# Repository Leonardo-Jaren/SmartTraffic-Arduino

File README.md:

# SmartTraffic Arduino

Sistema educativo para explorar una maqueta de seis intersecciones, simular vehículos y consultar un Arduino UNO por USB. El frontend usa Vue 3, Vite y Three.js; la API y el puente local usan Django REST Framework y pySerial.

La maqueta física mide **160 cm de ancho × 120 cm de fondo** según indicó el usuario; el tablero 3D se ajusta a ese tamaño. La distribución interna es una **aproximación** basada en el croquis. Las direcciones H1 ←, H2 →, V1 ↑, V2 ↓ y V3 ↑ fueron confirmadas. La escena base tiene exactamente seis semáforos fijos, uno por cruce, en los puntos y mirando en los sentidos marcados: S1→I1 al sur, S2→I2 al este, S3→I3 al sur, S4→I4 al oeste, S5→I5 al norte y S6→I6 al oeste. La simulación aplica la fase del eje observado en cada luz. El mapa eléctrico del Arduino no está confirmado y el sketch arranca en rojo hasta revisar el cableado.

## Requisitos

- Python 3.12 o superior compatible con las versiones de `backend/requirements.txt`.
- Node.js `^22.18.0` o `>=24.12.0`, npm y un navegador con WebGL.
- Para USB: Arduino UNO R3, cable USB de datos y permiso para acceder al puerto. Django y el puente deben ejecutarse en la computadora que tiene el Arduino conectado.

## Instalar y ejecutar

En una terminal, desde la raíz del repositorio:

```bash
cd backend
python3 -m venv env
./env/bin/python -m pip install -r requirements.txt
./env/bin/python manage.py migrate
./env/bin/python manage.py runserver 127.0.0.1:8000
```

En otra terminal:

```bash
cd frontend
npm ci
npm run dev
```

Abre la dirección local que Vite imprime en su terminal. En Windows sustituye `./env/bin/python` por `env\Scripts\python.exe`. Vite envía las peticiones `/api` a Django mediante su proxy de desarrollo. La API no tiene autenticación: esta configuración es **solo para desarrollo local** y no debe exponerse a Internet.

## Sin Arduino

Selecciona **Simulación**. Puedes pausar, reiniciar, ocultar vehículos, variar cantidad y velocidad, seleccionar y cerrar un tramo, seleccionar un cruce y añadir luces virtuales. Los vehículos buscan otra ruta o salida y, si no existe, esperan; un vehículo que ya está en un tramo cerrado se detiene. La tabla de intersecciones muestra fases virtuales H/V, no el estado físico de S1–S6.

Los autos frenan con el frente detrás de la línea, mantienen espacio en las colas y esperan antes de entrar si no hay lugar para salir del cruce. Un vehículo que ya recibió paso termina de despejarlo aunque cambie la fase. Las calles conservan un color neutro salvo selección o cierre; los colores de paso se muestran en las luces. Los accesos perpendiculares sin luz física tienen señales visuales de ceda el paso; la simulación sigue reservando fases H/V para evitar movimientos incompatibles.

Usa **Pantalla completa** sobre la maqueta para ampliar la vista y conservar los controles de simulación y selección. Puedes volver con el botón de salida o con Escape. Si el navegador no permite la pantalla completa nativa, la vista se amplía dentro de la ventana.

Selecciona S1–S6 en el modelo o en su tarjeta para cambiar su esquina dentro del cruce y girarlo en pasos de 90°. La distribución visual se guarda en este navegador y puede restaurarse. Estos movimientos no cambian el cruce asignado, el eje de simulación ni los pines del Arduino. Un traslado a otro cruce requiere revisar también esa asignación lógica y el montaje físico.

La escala de cálculo es **1 unidad 3D = 5 metros simulados**. Por ejemplo, a 30 km/h se recorren 8,33 m/s, es decir 1,67 unidades 3D/s. Esta conversión de velocidad es independiente del tamaño visual del tablero de 160 × 120 cm. Los desfases horizontales usan 30 km/h como velocidad objetivo virtual; no se ha validado una ola verde física.

## Conectar un Arduino por USB

1. Sigue [electrónica y conexiones](docs/ELECTRONICA.md) y [código Arduino](docs/CODIGO_ARDUINO.md). El sketch arranca en rojo mientras `MAPA_CONFIRMADO` sea `false`.
2. Conecta el UNO a la **misma computadora que ejecuta Django**. Cierra el monitor serial del IDE antes de abrir el puente.
3. En otra terminal del backend ejecuta:

```bash
./env/bin/python manage.py puente_serial --listar
./env/bin/python manage.py puente_serial --puerto /dev/ttyACM0
```

Reemplaza el puerto por el que aparezca en tu equipo, por ejemplo `COM3` en Windows. Selecciona **Dispositivo** en la web: solo se muestran colores informados recientemente por el dispositivo. Un cambio de tiempos queda pendiente hasta recibir `ACK, …, APLICADO`.

Para probar el puente sin hardware en Linux/macOS, ejecuta `./env/bin/python scripts/simulador_arduino.py`, toma el puerto `/dev/pts/...` que muestra y pásalo a `puente_serial --puerto`. La interfaz lo identifica como **simulador serial**, no como Arduino físico.

## Pruebas

```bash
cd backend && ./env/bin/python manage.py test trafico.tests
cd ../frontend && npm test && npm run build
npx playwright install chromium   # una vez, para las pruebas de navegador
npm run test:e2e
cd .. && python3 arduino/tests/test_firmware.py
```

Las pruebas de navegador reutilizan Django y Vite si ya están funcionando localmente, o los arrancan si faltan; en CI necesitan los puertos libres. Se puede indicar un Chromium ya instalado con `CHROMIUM_PATH=/ruta/a/chromium npm run test:e2e`. Los resultados y límites están en [pruebas](docs/PRUEBAS.md).

## Documentación

- [Configuración en otra computadora y exportación de la PCB](docs/CONFIGURACION.md)
- [Análisis de la maqueta y mapa](docs/ANALISIS_MAQUETA.md)
- [Electrónica y tabla de conexiones](docs/ELECTRONICA.md)
- [Guía visual PDF para soldar y conectar los seis semáforos](docs/GUIA_VISUAL_CONEXIONES_ARDUINO.pdf)
- [Código completo para Arduino IDE](docs/CODIGO_ARDUINO.md)
- [Arquitectura, protocolo y modos](docs/ARQUITECTURA.md)
- [Pruebas y limitaciones](docs/PRUEBAS.md)

La guía PDF conserva las orientaciones del diseño anterior con todos los ejes H. Para la posición y la cara actuales de cada semáforo usa [el mapa actualizado](docs/ANALISIS_MAQUETA.md); la correspondencia física de los pines sigue pendiente de comprobación.

El modelo es procedural en Three.js, con tramos y cruces seleccionables; no se exportó un GLB. La comunicación Wi-Fi con ESP32 es una arquitectura futura, no una funcionalidad implementada.

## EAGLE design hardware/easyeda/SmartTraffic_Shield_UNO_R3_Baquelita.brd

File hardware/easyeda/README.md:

# Shield SmartTraffic para Arduino UNO R3

## Variante para baquelita de una cara

- [PCB editable para EasyEDA Standard](SmartTraffic_Shield_UNO_R3_Baquelita_EasyEDA.json).
- [PCB editable en formato Eagle](SmartTraffic_Shield_UNO_R3_Baquelita.brd) y [su esquema con las nueve borneras](SmartTraffic_Shield_UNO_R3_Baquelita.sch).
- [Máscara exportada directamente desde EasyEDA](../../output/pdf/SmartTraffic_Borneras_EasyEDA_1a1.pdf) y [captura de la placa guardada](../../output/imagen/SmartTraffic_EasyEDA_Borneras.png).
- [PDF A4 a escala 1:1 con un único dibujo de cobre](../../output/pdf/SmartTraffic_PCB_Baquelita_1_Cara_1a1.pdf).
- [Vista ampliada de las pistas anchas y sus componentes](../../output/imagen/SmartTraffic_Baquelita_Pistas_Anchas.png). Las imágenes de `Vistas_SmartTraffic` muestran la revisión anterior con U1 SMD.

La baquelita se corta por el rectángulo exterior de **130 × 90 mm**. El UNO R3 de referencia (68,58 × 53,34 mm) queda centrado debajo del shield, con 30,71 mm a cada lado y 18,33 mm arriba y abajo. J1–J4 y los cuatro taladros de montaje conservan sus posiciones de apilado. X1–X6 quedan por encima de la fila digital y X7–X9 por debajo de la analógica, con la entrada de cable hacia el borde correspondiente. El traductor U1, J5, JP1, R1, C1 y C2 quedan a la derecha del UNO. El modelo del ESP32 y su soporte siguen pendientes.

Las 26 redes usan cobre inferior de 0,60 mm de ancho. La separación mínima entre pistas de redes distintas es 1,127 mm. Al incluir los pads, el mínimo nominal es 0,644 mm entre D2 y D3. El rectángulo en BoardOutLine es la línea mecánica de corte. El PDF A4 reúne esa línea, el cobre y las cuatro cruces de montaje en un solo dibujo a escala real.

U1 es el TXU0202DCUR montado sobre un adaptador VSSOP-8 a DIP-8 de paso 2,54 mm y 7,62 mm entre filas, como el PA0042 con pines instalados. Alinea el pin 1 del adaptador con el pad cuadrado de U1. R1 es axial de 10 kΩ con paso de 7,62 mm. C1 y C2 son cerámicos radiales de 100 nF con paso de 5,08 mm. El adaptador y los componentes pasantes se montan en la cara sin cobre. [Adaptador PA0042](https://www.proto-advantage.com/store/datasheets/PA0042.pdf)

Para revisar la versión nueva en EasyEDA Standard, usa **Archivo → Abrir → EasyEDA** con el JSON de baquelita. Comprueba que se vean los ocho orificios de U1 y ejecuta **Check DRC**. Para la transferencia, el PDF incluido usa la vista desde la cara sin cobre. Imprime en A4 al 100 %, coteja la barra de 50 mm y coloca el tóner hacia el cobre sin aplicar un espejo adicional. Marca el corte por el centro de la línea exterior y los cuatro taladros por sus cruces en la misma hoja A4. [DRC de EasyEDA](https://docs.easyeda.com/en/PCB/Design-Rule-Check/)

La máscara incluye guías blancas de 0,30 mm. El CAD indica taladros de 1,20 mm para X1–X9, 1,00 mm para U1 y las tiras, 0,80 mm para R1, C1 y C2, y 3,20 mm para el montaje. Comprueba los diámetros contra las patas y espadines reales. El [exportador](exportar_baquelita.py) coteja las redes con el esquema UART y comprueba continuidad con una pérdida de cobre simulada de 0,04 mm por borde y un margen de perforación de 0,10 mm. Para regenerar el PDF desde la raíz, ejecuta `python hardware/easyeda/exportar_baquelita.py` con ReportLab y Shapely instalados.

La PCB guardada en **Smart traffic** mostró 19 componentes, 26/26 redes y 0 errores de DRC. La máscara nativa se exportó con el borde, el cobre inferior y los pads multicapa en negro, sin espejo. A 600 ppp se cotejaron los 70 orificios y la conectividad entre todos los pares de pads con el esquema. La hoja A4 lleva una sola máscara y guías de perforación pequeñas para taladrar a mano. En ambos casos usa tamaño real. Antes de grabar, verifica la escala, el encaje en el UNO y el montaje de las piezas con la hoja A4.

### Borneras de señal X1–X9

La huella elegida corresponde a **Phoenix Contact 1984617, PT 1,5/2-3,5-H**. Paso de 3,50 mm, cuerpo de 7,00 × 7,55 mm, taladro de 1,20 mm. Ambas filas dejan 3,00 mm nominales entre los cuerpos de borneras vecinas. Presenta las nueve piezas en papel y comprueba acceso del cable y del destornillador con los conectores instalados. Las piezas de 5,00 o 5,08 mm requieren otro patrón. [Ficha del fabricante](https://www.phoenixcontact.com/en-lt/products/printed-circuit-board-terminal-pt-15-2-35-h-1984617)

| Bornera | Pad 1 cuadrado | Pad 2 redondo |
| --- | --- | --- |
| X1 | D13 | D12 |
| X2 | D11 | D10 |
| X3 | D9 | D8 |
| X4 | D7 | D6 |
| X5 | D5 | D4 |
| X6 | D3 | D2 |
| X7 | A0 | A1 |
| X8 | A2 | A3 |
| X9 | A4 (SDA) | A5 (SCL) |

D0/RX y D1/TX pasan por el traductor U1 hasta J5 y quedan reservados para el ESP32. A0 y A1 son pines diferentes. Cada tornillo de X1–X9 lleva **una señal independiente**. El par de tornillos de una bornera carece de retorno común. D13 comparte el LED integrado del UNO. A4/A5 también sirven para I²C y se previeron para supervisión. Su acceso en X9 permite medirlos. Confirma su función antes de asignarlos a luces.

Las borneras entregan GPIO directos. Antes de conectar un foco comprueba polaridad, resistencia instalada, corriente por salida, por puerto y total, retorno y fuente de luces. Si la carga requiere driver, conecta la señal del borne a la entrada del driver y alimenta las luces desde la etapa dimensionada. Mantén la resistencia que ya lleva cada LED. Las luces individuales S1–S9 quedan pendientes del mapa físico y de las mediciones. S4 y S6 requieren salidas independientes.

### Encaje sobre el UNO R3

La comparación con el [CAD oficial A000066](https://docs.arduino.cc/hardware/uno-rev3) verificó la posición de los 32 contactos de J1–J4 y de los cuatro agujeros de montaje. Visto desde arriba con el USB a la izquierda, el pad cuadrado de J1 corresponde a D8 y el de J2 a D0/RX. Los pads cuadrados de J3 y J4 quedan a la izquierda y corresponden a la posición sin conexión de POWER y a A0. Entre los contactos más próximos de J1 y J2 hay 4,064 mm de centro a centro. Usa cuatro tiras separadas para respetar esa separación. [Pinout del UNO R3](https://docs.arduino.cc/resources/pinouts/A000066-full-pinout.pdf)

Para comprobar el apilado y el corte de esta variante, imprime la [hoja de 130 × 90 mm](../../output/pdf/SmartTraffic_PCB_Baquelita_1_Cara_1a1.pdf) al 100 % y mide la barra de 50 mm. Presenta las cuatro tiras en el UNO apagado y verifica que el papel calce sin forzarlas. Después mide la separación con las tiras que vas a soldar. Las soldaduras y las puntas de las patas pasantes quedan del lado del cobre, hacia el UNO. Comprueba la holgura sobre el USB-B, el jack DC, el ATmega328P y ambos ICSP, incluido el que queda junto al USB. El contorno también cubre el botón RESET. Revisa el acceso si necesitas accionarlo con el shield puesto. Si algo toca, elige tiras más altas y repite la prueba antes de transferir el cobre.

## Diseño de referencia de dos caras

Borrador para EasyEDA Standard. El proyecto existente **Smart traffic** contiene el esquema `Sheet_1` y la PCB `SmartTraffic_Shield_UNO_R3`. Para repetir la importación desde los archivos locales, abre **Archivo → Abrir → Eagle**.

La [PCB nativa de EasyEDA](SmartTraffic_Shield_UNO_R3_EasyEDA.json) conserva la revisión exportada del lienzo. Ábrela con **Archivo → Abrir → EasyEDA**. El [PDF A4 a escala 1:1](../../output/pdf/SmartTraffic_PCB_Escala_1a1.pdf) incluye ambas caras para comprobar el encaje en papel. Los archivos Eagle conservan las leyendas del borrador. La revisión nativa exportada carecía de esas dos leyendas de serigrafía.

La PCB contiene los diez componentes del esquema, ocho redes trazadas y un plano inferior de GND. EasyEDA mostró **8/8 redes y 0 errores de DRC** con las reglas del borrador. La comprobación geométrica local encontró continuidad y una separación mínima de 0,170 mm entre cobres de redes distintas. Habrá que repetir el DRC con las reglas del fabricante cuando estén todas las salidas. [Guía de importación](https://docs.easyeda.com/en/Import/Import-Eagle/) · [DRC de EasyEDA](https://docs.easyeda.com/en/PCB/Design-Rule-Check/)

La extracción de bibliotecas notificó siete símbolos rechazados, aunque las diez referencias y sus huellas quedaron visibles en el esquema y la PCB guardados. Al comparar ambos documentos, EasyEDA mostró que los componentes coincidían. La única propuesta fue añadir 28 redes de un solo pin para los contactos del UNO pendientes de asignar. La comparación se cerró sin aplicar esos cambios.

El contorno de 68,58 × 53,34 mm, los cuatro agujeros de 3,2 mm y las posiciones de J1–J4 proceden del CAD **UNO-TH Rev3e** de Arduino. Los centros de las cuatro tiras coinciden con el CAD. Las zonas del USB-B, el jack DC y el ICSP están marcadas en la capa de documentación para comprobar la altura libre al apilar el shield. Los taladros de 1 mm de las tiras se deben cotejar con el conector que se vaya a usar. La geometría adaptada del CAD de Arduino conserva su licencia CC BY-SA 4.0. [CAD del UNO R3](https://docs.arduino.cc/hardware/uno-rev3) · [Licencia](https://creativecommons.org/licenses/by-sa/4.0/)

## UART propuesta

El TXU0202 traduce las señales de 5 V del UNO y de 3,3 V del ESP32 en ambos sentidos. Su lado de 5 V toma alimentación del UNO y el lado de 3,3 V recibe la referencia del ESP32 en J5. Cada lado tiene un condensador de 100 nF. El ESP32 requiere su propia alimentación, dimensionada para el módulo elegido. [Aplicación UART de Texas Instruments](https://www.ti.com/lit/ds/symlink/txu0202.pdf)

| J5 | Conexión del lado ESP32 |
| --- | --- |
| 1 | GND común |
| 2 | Referencia de 3,3 V para el traductor |
| 3 | RX del ESP32 |
| 4 | TX del ESP32 |

Deja JP1 abierto durante la carga del sketch o el uso del puerto serie por USB. R1 mantiene el traductor deshabilitado con el puente abierto. Cierra JP1 para usar la UART con el ESP32 cuando el puerto serie USB esté libre. El conversor USB del UNO comparte D0 y D1. [Esquema oficial del UNO R3](https://docs.arduino.cc/resources/schematics/A000066-schematics.pdf)

## Reparto provisional de salidas

El punto de partida son **27 canales independientes**. S4 y S6 necesitan tiempos distintos para la ola verde. Cualquier agrupación posterior requiere demostrar coincidencia por color durante fases, cierres, arranque y pruebas individuales.

El UNO conserva el control del calendario de fases y el ESP32 mantiene el enlace Wi-Fi y aplica las fases de los cruces delegados. Mantener juntas las luces de un mismo cruce permite ejecutar el amarillo y el intervalo de todo rojo con un solo reloj local.

| Equipo de referencia | Canales para luces | Comunicación y reserva |
| --- | --- | --- |
| UNO R3 | 15 con D2–D12 y A0–A3 como salidas digitales | D0/D1 para UART. A4/A5 para supervisión. D13 queda disponible para una función que tolere el LED de la placa. |
| ESP32-S3-DevKitC-1 | 12 con GPIO4–GPIO15 | GPIO16/17 como candidatos a RX/TX de una UART adicional. GPIO18/21 para supervisión. |

Con el croquis del repositorio como hipótesis, el UNO puede llevar los dos cruces con S4 y S6 completos más un cruce de un solo semáforo. El ESP32 puede llevar el tercer cruce con dos semáforos y los otros dos cruces de una sola cabeza. El esquema todavía carece de asignaciones de los LED a estos pines. El reparto 18/9 también cubre las luces, pero ocupa las 18 E/S del UNO disponibles tras reservar la UART. [Pinout del UNO R3](https://docs.arduino.cc/resources/pinouts/A000066-full-pinout.pdf) · [Pines del ESP32-S3-DevKitC-1](https://docs.espressif.com/projects/esp-dev-kits/en/latest/esp32s3/esp32-s3-devkitc-1/user_guide_v1.1.html)

### Cruces según el croquis v2.1 del repositorio

| Cruce | Semáforos y sentido regulado según el croquis |
| --- | --- |
| I1 | S1, V1 hacia el norte |
| I2 | S2, H1 hacia el oeste. S7, V2 hacia el sur. |
| I3 | S3, V3 hacia el norte |
| I4 | S4, H2 hacia el este. S8, V1 hacia el norte. |
| I5 | S5, V2 hacia el sur |
| I6 | S6, H2 hacia el este. S9, V3 hacia el norte. |

En `origin/main` (`46bfede`), S7–S9 son contrapartes de la simulación. El firmware físico controla S1–S6 y conserva `MAPA_CONFIRMADO=false`. La guía electrónica documenta un UNO R3 y resistencias de 2,2 kΩ en serie con LED de cátodo a GND. Las pruebas registradas indican que la placa, las resistencias y el cableado del montaje no se comprobaron. [Croquis v2.1](../../docs/ANALISIS_MAQUETA.md) · [Guía electrónica](../../docs/ELECTRONICA.md) · [Pruebas registradas](../../docs/PRUEBAS.md)

### Alternativa con decodificación por cruce

Un decodificador por cruce permite conservar los **27 canales de lámpara** con **15 señales de fase**. Cada cruce con dos semáforos usa tres bits y cada cruce con un semáforo usa dos. Con el reparto provisional anterior, serían ocho señales de fase en el UNO y siete en el ESP32, más UART y supervisión. S4 y S6 seguirían en decodificadores distintos. El [esquema de referencia](SmartTraffic_Decodificador_Cruce.sch) se abre desde **Archivo → Abrir → Eagle** y contiene un módulo independiente para probar en banco.

| Código binario del cruce doble | Semáforo A | Semáforo B |
| --- | --- | --- |
| `000` | Rojo | Rojo |
| `001` | Verde | Rojo |
| `010` | Rojo | Rojo |
| `011` | Amarillo | Rojo |
| `100` | Rojo | Rojo |
| `101` | Rojo | Rojo |
| `110` | Rojo | Verde |
| `111` | Rojo | Amarillo |

El SN74AHCT138 toma los bits en `C/B/A` (pines 3/2/1) y entrega `Y1` y `Y3` para verde y amarillo del primer semáforo, y `Y6` y `Y7` para el segundo. Son salidas activas en bajo. Para el circuito de mando de lado alto, `NAND(Y1,Y3)` y `NAND(Y6,Y7)` dan los mandos de rojo, también activos en bajo. En un cruce simple se fija `C=0` y solo se usa el primer par. El umbral alto de las entradas AHCT es 2 V con la alimentación recomendada de 4,5 a 5,5 V, por lo que el mando de 3,3 V es compatible si el módulo elegido garantiza ese nivel bajo carga. [Decodificador SN74AHCT138](https://www.ti.com/lit/ds/symlink/sn74ahct138.pdf) · [Compuertas SN74AHCT00](https://www.ti.com/product/SN74AHCT00)

Con `PERMISO=0` o `FALLO=1`, el decodificador deja todas las `Y` en alto. Los mandos de verde y amarillo quedan inactivos y las dos NAND piden rojo. En el módulo de prueba, 10 kΩ lleva `PERMISO` a GND y otros 10 kΩ llevan `FALLO` a 5 V cuando las entradas están abiertas. El supervisor debe manejar `FALLO` con una salida de drenador abierto que tolere 5 V. J2 entrega mandos lógicos activos en bajo para los drivers.

Un monoestable redisparable CD74HCT423 es candidato para que el permiso caduque y quede inactivo sin pulsos válidos. Su entrada de borrado debe mantenerlo inactivo durante el arranque, el reset y mientras el mapa esté bloqueado. El ESP32 debe dejar de renovar su permiso cuando pierda las órdenes válidas del UNO. La aplicación debe mostrar el estado de dispositivo solo mientras esté confirmado y vigente. [Monoestable CD74HCT423](https://www.ti.com/product/CD74HCT423)

El ciclo `000 → 001 → 011 → 010 → 110 → 111 → 101 → 100 → 000` cambia un solo bit en cada paso. El firmware mantiene el amarillo y el intervalo de todo rojo correspondiente antes de avanzar. Las órdenes de cierre, recuperación y prueba deben pasar por estados rojos válidos. Se verificaron por tabla todos los códigos con permiso habilitado y deshabilitado, además de la secuencia normal para uno y dos semáforos. El retardo de propagación de la lógica y los transitorios de arranque requieren comprobar en banco que las etapas de salida inhiban amarillo y verde durante las conmutaciones y mantengan rojo mientras el circuito de luces tenga tensión suficiente.

### Driver de prueba para retorno común a GND

El [esquema del driver de lado alto](SmartTraffic_Driver_Lado_Alto.sch) desarrolla un semáforo del croquis con fuente regulada de 5 V. Usa un SN74AHCT125 con salida de alta impedancia y tres MOSFET P PMV48XP. La fuente de cada MOSFET va a 5 V y el drenador alimenta su LED a través de la resistencia ya instalada en el cableado. [Buffer SN74AHCT125](https://www.ti.com/lit/ds/symlink/sn74ahct125.pdf) · [MOSFET PMV48XP](https://assets.nexperia.com/documents/data-sheet/PMV48XP.pdf)

El supervisor debe llevar `OE_N` a bajo solo con permiso válido y sin fallo, mediante una salida de drenador abierto tolerante a 5 V. Con `OE_N` alto o abierto, el buffer queda en alta impedancia. Las resistencias de compuerta fijan rojo encendido y amarillo y verde apagados una vez que la alimentación es suficiente. Las otras resistencias pertenecen al circuito de mando. Un montaje con ánodo común requiere una etapa de lado bajo.

En banco, comprueba primero que al soltar `OE_N` se active solo rojo. Después conecta los tres mandos del decodificador y prueba cada fase, la caída del permiso, el reset y la subida y caída de la alimentación. Mide tensión y corriente en los LED, y observa las conmutaciones para descartar destellos simultáneos. El esquema representa un semáforo de tres colores y queda pendiente de integrar en la PCB principal tras validar la carga y el supervisor.

## Desfase de la ola verde

La velocidad objetivo que se quiere representar es **30 km/h**. Quedan pendientes las distancias por el carril entre líneas de parada I4→I5 e I5→I6, la escala física y la velocidad de los vehículos de maqueta. Para vehículos físicos, divide la distancia de cada tramo en centímetros entre la velocidad medida en cm/s. Si se usa una escala 1:N con el objetivo de 30 km/h, el tiempo de cada tramo en segundos es `distancia_cm × N × 0,0012`. Suma los tiempos para obtener el desfase acumulado de I6 respecto a I4 y aplica el resto del ciclo cuando corresponda. Con los tiempos calculados, verifica que las llegadas queden dentro del verde y que se conserven el amarillo y el intervalo de todo rojo de cada cruce.

El tablero documentado mide 160 × 120 cm. La simulación actual usa 14 unidades entre cruces consecutivos, 4 m simulados por unidad y 45 km/h. Eso da 4,48 s por tramo virtual y 8,96 s de I4 a I6. Las distancias físicas y la velocidad de la maqueta siguen pendientes. [Mapa de la simulación](../../frontend/src/composables/simulacion/mapa.ts) · [Cálculo de fases](../../frontend/src/composables/simulacion/luces.ts)

## Antes de fabricar

- Confirma el modelo y la alimentación del ESP32, y comprueba la UART en ambos sentidos, con JP1 abierto durante la programación y con cada placa alimentada por separado.
- Verifica el cruce y el sentido de S1 a S9. Agrupa únicamente luces que coincidan durante las fases, los intervalos de todo rojo, los cierres y el modo de prueba. El firmware actual todavía direcciona las pruebas por semáforo individual.
- Identifica el valor de cada resistencia con el circuito sin alimentación. Con el LED encendido a la tensión prevista, mide la caída en esa resistencia y calcula la corriente como `I = V / R`. Dimensiona cada canal con esa corriente o la suma de ramas si se valida un grupo. Comprueba el consumo total durante todo rojo (la suma de los nueve rojos) y en cada estado permitido. Para los drivers, comprueba caída de tensión, capacidad por canal y capacidad total, y elige la topología según la polaridad y los retornos del cableado.
- Implementa y prueba el arranque en rojo, incluso durante el reset del UNO. Mantén bloqueado el ciclo automático hasta verificar el mapa. Completa el ruteo, ejecuta ERC y DRC y verifica el encaje en el UNO físico.

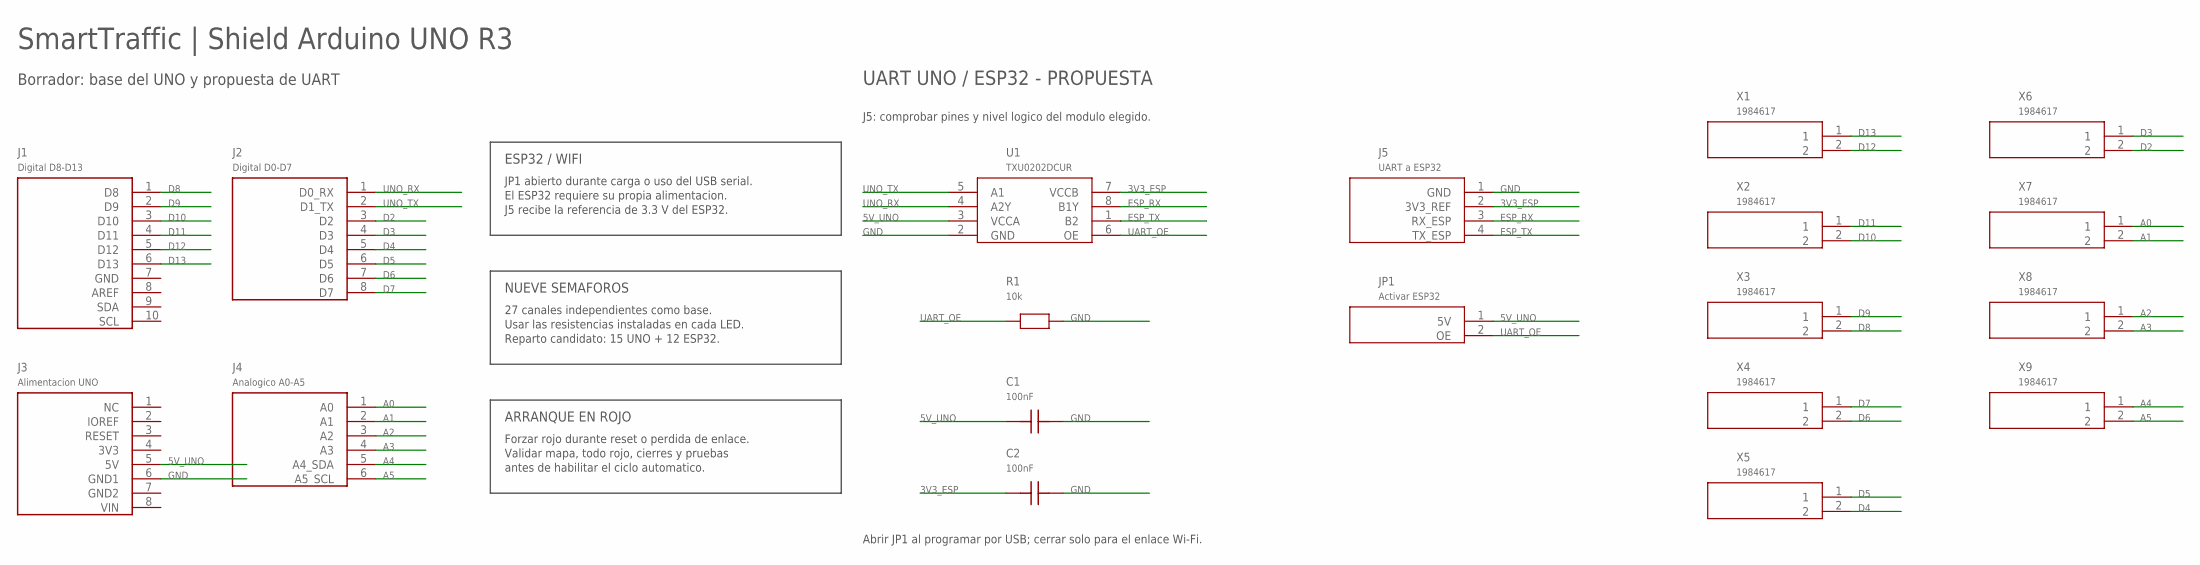
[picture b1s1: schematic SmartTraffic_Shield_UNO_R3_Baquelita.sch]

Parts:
C1, C2: 100nF; CAPACITOR_RADIAL_5_08MM
J1: Digital D8-D13; SHIELD_1X10_P2.54
J2: Digital D0-D7; SHIELD_1X08_P2.54
J3: Alimentacion UNO; SHIELD_1X08_P2.54
J4: Analogico A0-A5; SHIELD_1X06_P2.54
J5: UART a ESP32; SHIELD_1X04_P2.54
JP1: Activar ESP32; SHIELD_1X02_P2.54
R1: 10k; RESISTENCIA_AXIAL_7_62MM
U1: TXU0202DCUR; TXU0202_ADAPTADOR_DIP8_300MIL
X1, X2, X3, X4, X5, X6: 1984617; PT_1_5_2_3_5_H
X7, X8, X9: 1984617; PT_1_5_2_3_5_H_SUR

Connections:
3V3_ESP: C2.1, J5.2 (3V3_REF), U1.7 (VCCB)
5V_UNO: C1.1, J3.5 (5V), JP1.1 (5V), U1.3 (VCCA)
A0: J4.1 (A0), X7.1
A1: J4.2 (A1), X7.2
A2: J4.3 (A2), X8.1
A3: J4.4 (A3), X8.2
A4: J4.5 (A4_SDA), X9.1
A5: J4.6 (A5_SCL), X9.2
D2: J2.3 (D2), X6.2
D3: J2.4 (D3), X6.1
D4: J2.5 (D4), X5.2
D5: J2.6 (D5), X5.1
D6: J2.7 (D6), X4.2
D7: J2.8 (D7), X4.1
D8: J1.1 (D8), X3.2
D9: J1.2 (D9), X3.1
D10: J1.3 (D10), X2.2
D11: J1.4 (D11), X2.1
D12: J1.5 (D12), X1.2
D13: J1.6 (D13), X1.1
ESP_RX: J5.3 (RX_ESP), U1.8 (B1Y)
ESP_TX: J5.4 (TX_ESP), U1.1 (B2)
GND: C1.2, C2.2, J3.6 (GND1), J5.1 (GND), R1.2, U1.2 (GND)
UART_OE: JP1.2 (OE), R1.1, U1.6 (OE)
UNO_RX: J2.1 (D0_RX), U1.4 (A2Y)
UNO_TX: J2.2 (D1_TX), U1.5 (A1)

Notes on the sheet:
SmartTraffic | Shield Arduino UNO R3
Borrador: base del UNO y propuesta de UART
ESP32 / WIFI
JP1 abierto durante carga o uso del USB serial.
El ESP32 requiere su propia alimentacion.
J5 recibe la referencia de 3.3 V del ESP32.
NUEVE SEMAFOROS
27 canales independientes como base.
Usar las resistencias instaladas en cada LED.
Reparto candidato: 15 UNO + 12 ESP32.
ARRANQUE EN ROJO
Forzar rojo durante reset o perdida de enlace.
Validar mapa, todo rojo, cierres y pruebas
antes de habilitar el ciclo automatico.
UART UNO / ESP32 - PROPUESTA
J5: comprobar pines y nivel logico del modulo elegido.
Abrir JP1 al programar por USB; cerrar solo para el enlace Wi-Fi.

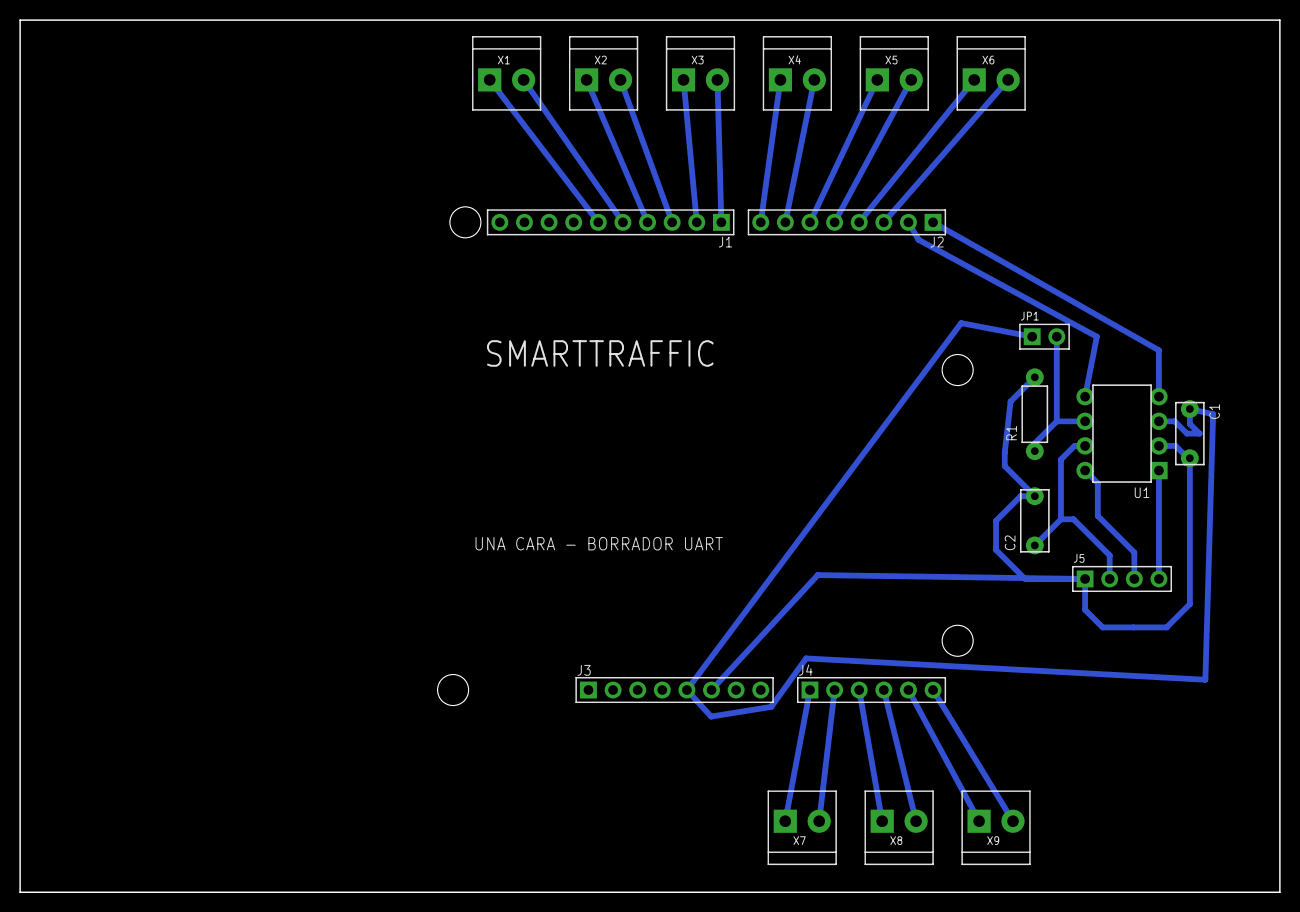
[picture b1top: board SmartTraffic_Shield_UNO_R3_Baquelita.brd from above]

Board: 2 copper layers, 130.0 x 90.0 mm, 19 parts (0 on the bottom side), 26 nets.
